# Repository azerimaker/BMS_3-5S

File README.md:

# BMS 3-5S
3-5S Battery Management System based on TI bq76920 IC and MSP430 uC. The design is largely influenced by the TI's [TIDA-00449](http://www.ti.com/tool/TIDA-00449) reference and LibreSolar's excellent [BMS-5s](https://github.com/LibreSolar/BMS-5s) designs.

## Specs:
- 3-5 Li-ion/Po Cells
- MSP430 Microcontroller for gas gauging, balancing and serial communication
- Load current: 50A (cont.), 100A (peak) (estimated!)
- You can find the PCB on Seeedstudio's [Fusion Gallery](https://www.seeedstudio.com/BMS-3-5S-g-1092928)

## Programming
- I'm using MSP430 Launchpad both to program the BMS in external target mode and to provide serial communication to PC. 

## Demo
- After modifying the TIDA-00449 firmware, which was designed for bq76930 (10S version) balancing and status report worked fine [(see here)](https://twitter.com/OrkhanAmirAslan/status/1014643359699406849)

## To Do in next Rev. 
- Add simple Python script to decode serial messages and print cell status
- Fix issues with battery voltage switching and Pre-Discharge mosfets. 
- Remove soldermask for high current tracks. 
- More pads for balancing resistors for higher power dissipation. 

<div align="center">
<br /> This work is licensed under a <a rel="license" href="http://creativecommons.org/licenses/by-sa/4.0/">Creative Commons Attribution-ShareAlike 4.0 International License</a>.

</div>

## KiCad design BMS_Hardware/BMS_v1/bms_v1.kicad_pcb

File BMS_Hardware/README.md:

## BMS 3-5S Hardware Files

KiCAD version 4.0.7 was used.

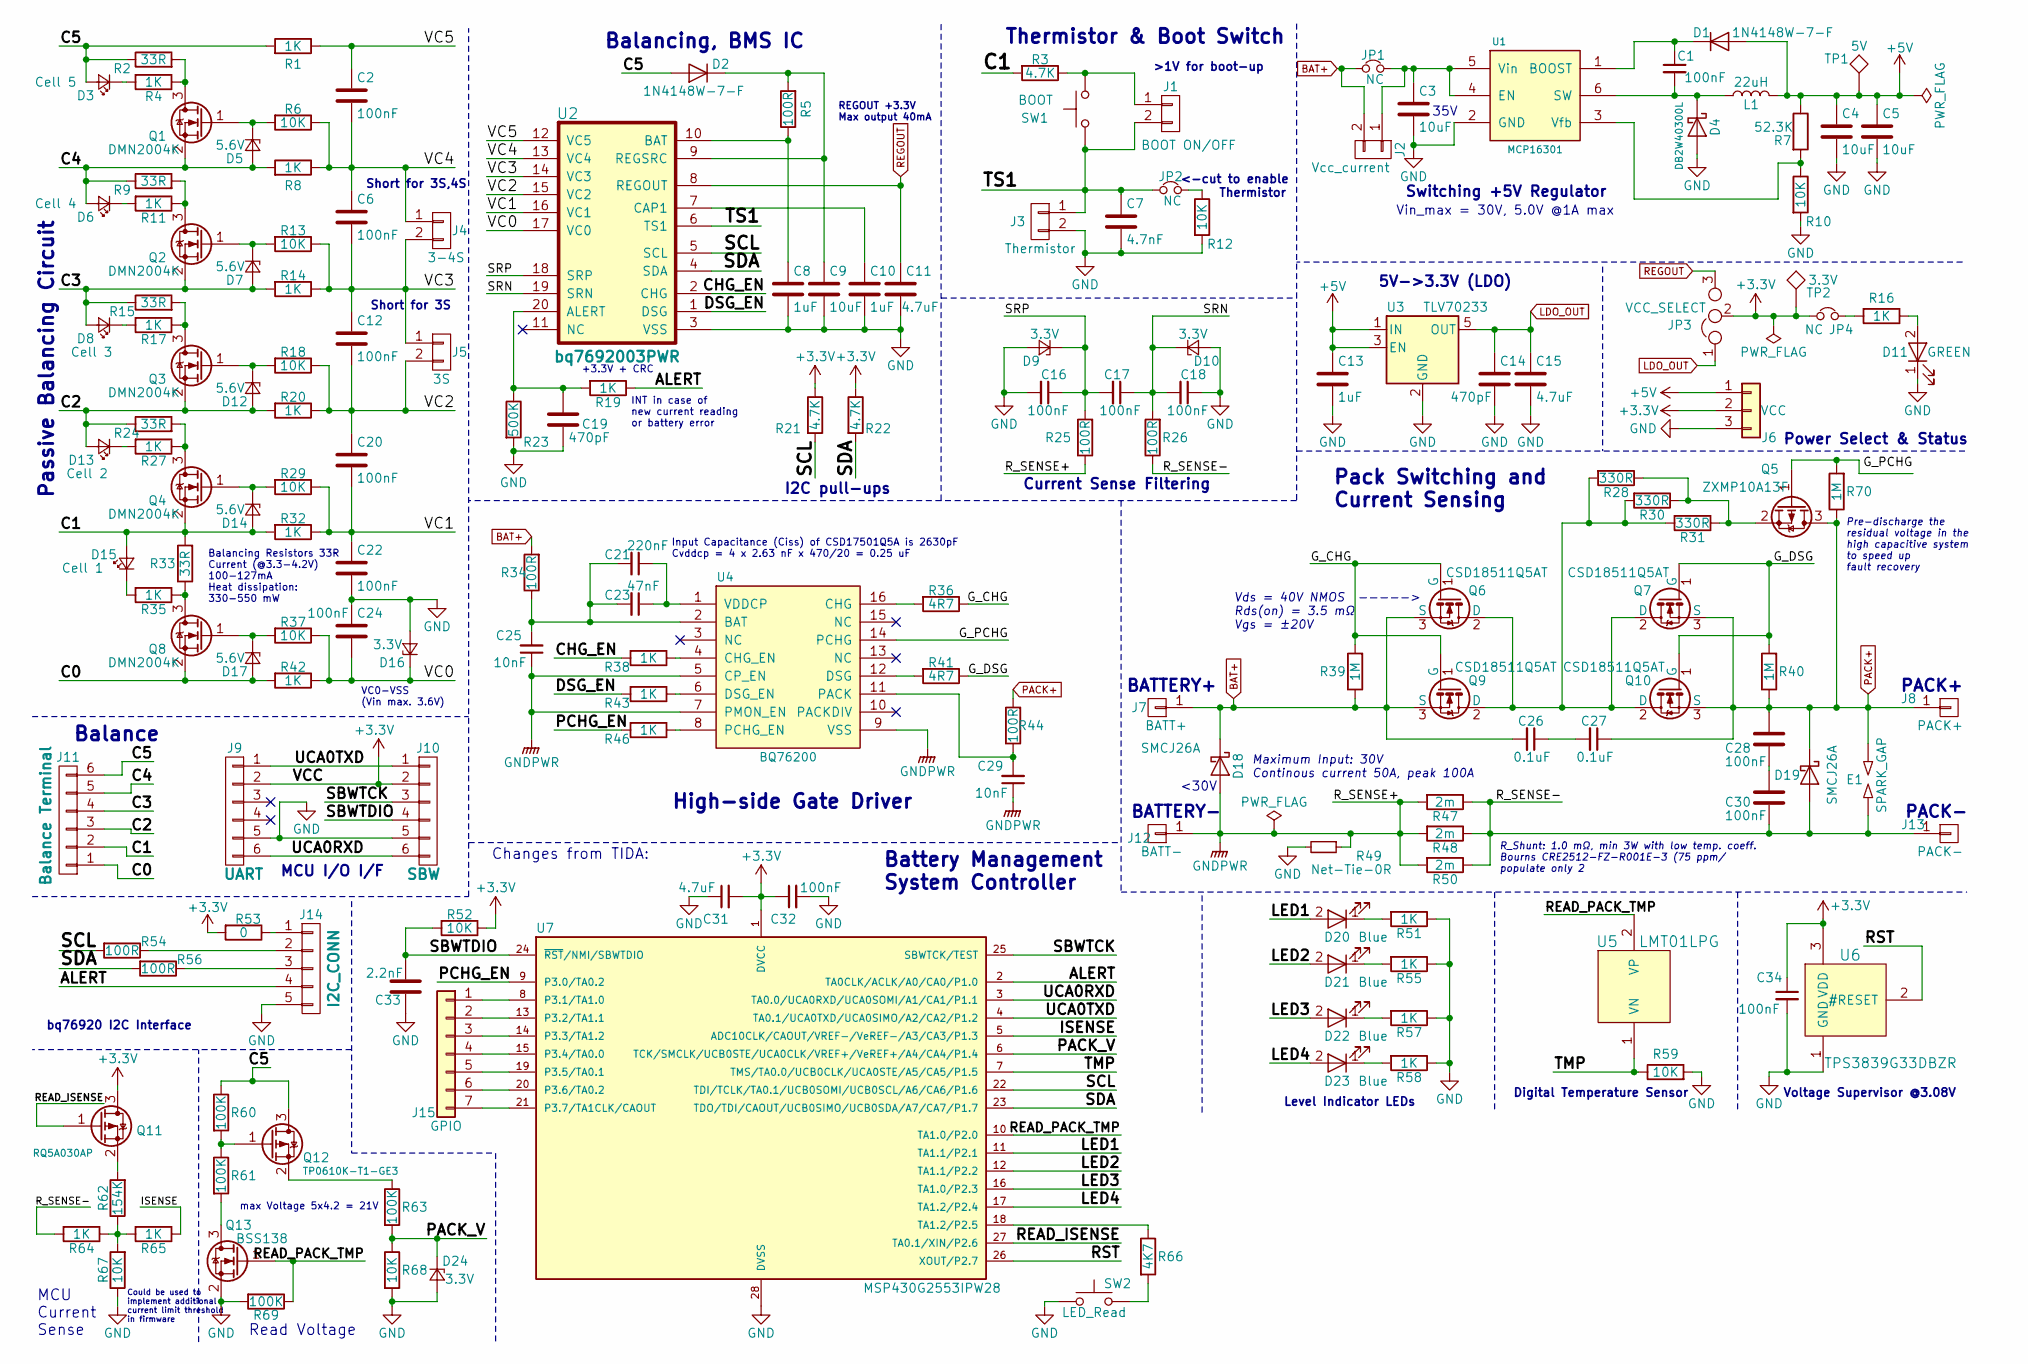
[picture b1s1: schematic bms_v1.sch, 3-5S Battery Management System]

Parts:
C1, C2, C6, C12, C16, C17, C18, C20, C22, C24, C28, C30, C32, C34: 100nF; C_0603
C3, C4, C9: 10uF; C_1210
C5: 10uF; C_0603
C7: 4.7nF; C_0603
C8, C10, C13: 1uF; C_0603
C11, C15, C31: 4.7uF; C_1206
C14, C19: 470pF; C_0603
C21: 220nF; C_0603
C23: 47nF; C_0603
C25, C29: 10nF; C_0603
C26, C27: 0.1uF; C_0603
C33: 2.2nF; C_0603
D1, D2: 1N4148W-7-F; D_SOD-123
D3: Cell 5; LED_0603
D4: DB2W40300L; D_SOD-123F
D5, D7, D12, D14, D17: 5.6V; D_SOD-323
D6: Cell 4; LED_0603
D8: Cell 3; LED_0603
D9, D10, D16, D24: 3.3V; D_SOD-323
D11: GREEN; LED_0603
D13: Cell 2; LED_0603
D15: Cell 1; LED_0603
D18, D19: SMCJ26A; D_SMC
D20, D21, D22, D23: Blue; LED_0603
E1: SPARK_GAP; Spark_Gap_1.65x1.1
J1: BOOT ON/OFF; jumper_NO
J2: Vcc_current; Pin_Header_Straight_1x02_Pitch2.54mm
J3: Thermistor; Test_Point_2Pads
J4: 3-4S; Pin_Header_Straight_1x02_Pitch2.54mm
J5: 3S; Pin_Header_Straight_1x02_Pitch2.54mm
J6: VCC; Pin_Header_Straight_1x03_Pitch2.54mm
J7: BATT+; MountingHole_3.5mm_Pad_Via
J8: PACK+; MountingHole_3.5mm_Pad_Via
J9: UART; Pin_Header_Straight_1x06_Pitch2.54mm
J10: SBW; Pin_Header_Straight_1x06_Pitch1.27mm
J11: Balance Terminal; PhoenixContact_MSTBVA-G_06x5.00mm_Vertical
J12: BATT-; MountingHole_3.5mm_Pad_Via
J13: PACK-; MountingHole_3.5mm_Pad_Via
J14: I2C_CONN; Pin_Header_Straight_1x05_Pitch2.54mm
J15: GPIO; Pin_Header_Straight_1x07_Pitch2.54mm
JP1, JP2, JP4: NC; jumper_NC
JP3: VCC_SELECT; JP_NO_NC
L1: 22uH; L_Taiyo-Yuden_NR-60xx
Q1, Q2, Q3, Q4, Q8: DMN2004K; SOT-23
Q5: ZXMP10A13F; SOT-23
Q6, Q7, Q9, Q10: CSD18511Q5AT; VSONP-8-1EP_5x6_Pitch1.27mm(GDS)
Q11: RQ5A030AP; SuperSOT-3
Q12: TP0610K-T1-GE3; SOT-23
Q13: BSS138; SOT-23
R1, R4, R8, R11, R14, R16, R17, R19, R20, R27, R32, R35, R38, R42, R43, R46, R51, R55, R57, R58, R64, R65: 1K; R_0603
R2, R9, R15, R24, R33: 33R; R_2010_HandSoldering
R3, R21, R22: 4.7K; R_0603
R5, R25, R26, R34, R44, R54, R56: 100R; R_0603
R6, R10, R12, R13, R18, R29, R37, R52, R59, R67, R68: 10K; R_0603
R7: 52.3K; R_0603
R23: 500K; R_0603
R28, R30, R31: 330R; R_0603_HandSoldering
R36, R41: 4R7; R_0603
R39, R40, R70: 1M; R_0603
R47, R48, R50: 2m; R_2512_HandSoldering
R49: Net-Tie-0R; R_0603_HandSoldering
R53: 0; R_0603
R60, R61, R63, R69: 100K; R_0603
R62: 154K; R_0603
R66: 4K7; R_0603
SW1: BOOT; SW_SPST_EVQP2
SW2: LED_Read; SW_SPST_EVQP2
TP1: 5V; Measurement_Point_Round-SMD-Pad_Small
TP2: 3.3V; Measurement_Point_Round-SMD-Pad_Small
U1: MCP16301; SOT-23-6
U2: bq7692003PWR; TSSOP-20_4.4x6.5mm_Pitch0.65mm
U3: TLV70233; SOT-23-5
U4: BQ76200; TSSOP-16_4.4x5mm_Pitch0.65mm
U5: LMT01LPG; Test_Point_2Pads
U6: TPS3839G33DBZR; SOT-23-3
U7: MSP430G2553IPW28; TSSOP-28_4.4x9.7mm_Pitch0.65mm

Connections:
+3V3: C31.2, C32.1, C34.1, J6.2, J9.2, J10.2, JP3.2, JP4.1, Q11.3 (D), R21.1, R22.1, R52.1, R53.2, TP2.1, U6.3 (VDD), U7.1 (DVCC)
+5V: C4.1, C5.1, C13.1, D1.2 (A), J6.1, L1.2, R7.1, TP1.1, U3.1 (IN), U3.3 (EN)
/ALERT: J14.4, R19.1, U7.2 (TA0CLK/ACLK/A0/CA0/P1.0)
/C0: D17.2 (A), J11.1, Q8.2 (S), R42.2
/C1: D14.2 (A), D15.2 (A), J11.2, Q4.2 (S), R3.2, R32.2, R33.2
/C2: D12.2 (A), D13.2 (A), J11.3, Q3.2 (S), R20.2, R24.1
/C3: D7.2 (A), D8.2 (A), J11.4, Q2.2 (S), R14.2, R15.1
/C4: D5.2 (A), D6.2 (A), J11.5, Q1.2 (S), R8.2, R9.1
/C5: D2.2 (A), D3.2 (A), J11.6, Q12.3 (D), R1.2, R2.1, R60.1
/CHG_EN: R38.2, U2.2 (CHG)
/DSG_EN: R43.2, U2.1 (DSG)
/G_CHG: Q6.1 (G), Q9.1 (G), R36.1, R39.2
/G_DSG: Q7.1 (G), Q10.1 (G), R40.2, R41.1
/ISENSE: R65.1, U7.5 (ADC10CLK/CAOUT/VREF-/VeREF-/A3/CA3/P1.3)
/LED1: D20.2 (A), U7.11 (TA1.1/P2.1)
/LED2: D21.2 (A), U7.12 (TA1.1/P2.2)
/LED3: D22.2 (A), U7.16 (TA1.0/P2.3)
/LED4: D23.2 (A), U7.17 (TA1.2/P2.4)
/PACK_V: D24.1 (K), R63.2, R68.1, U7.6 (TCK/SMCLK/UCB0STE/UCA0CLK/VREF+/VeREF+/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)
/PCHG_EN: R46.2, U7.9 (P3.0/TA0.2)
/READ_ISENSE: Q11.1 (G), U7.27 (TA0.1/XIN/P2.6)
/READ_PACK_TMP: Q13.1 (G), R69.1, U5.2 (VP), U7.10 (TA1.0/P2.0)
/RST: U6.2 (#RESET), U7.26 (XOUT/P2.7)
/R_SENSE-: C30.2, D19.2 (A), E1.2, J13.1, R26.1, R47.1, R48.1, R50.1, R64.2
/SBWTCK: J10.3, U7.25 (SBWTCK/TEST)
/SBWTDIO: C33.1, J10.4, R52.2, U7.24 (~RST~/NMI/SBWTDIO)
/SCL: R21.2, R54.2, U2.5 (SCL), U7.22 (TDI/TCLK/TA0.1/UCB0SOMI/UCB0SCL/A6/CA6/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)
/SDA: R22.2, R56.2, U2.4 (SDA), U7.23 (TDO/TDI/CAOUT/UCB0SIMO/UCB0SDA/A7/CA7/P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)
/SRN: C17.1, C18.2, D10.1 (K), R26.2, U2.19 (SRN)
/SRP: C16.1, C17.2, D9.1 (K), R25.2, U2.18 (SRP)
/TMP: R59.1, U5.1 (VN), U7.7 (TMS/TA0.0/UCB0CLK/UCA0STE/A5/CA5/P1.5)
/TS1: C7.1, J1.2, J3.1, JP2.1, SW1.2, U2.6 (TS1)
/UCA0RXD: J9.6, J10.6, U7.3 (TA0.0/UCA0RXD/UCA0SOMI/A1/CA1/P1.1)
/UCA0TXD: J9.1, J10.1, U7.4 (TA0.1/UCA0TXD/UCA0SIMO/A2/CA2/P1.2)
/VC0: C24.2, D16.1 (K), R37.1, R42.1, U2.17 (VC0)
/VC1: C20.2, C22.1, R29.1, R32.1, U2.16 (VC1)
/VC2: C12.2, C20.1, J5.2, R18.1, R20.1, U2.15 (VC2)
/VC3: C6.2, C12.1, J4.2, J5.1, R13.1, R14.1, U2.14 (VC3)
/VC4: C2.2, C6.1, J4.1, R6.1, R8.1, U2.13 (VC4)
/VC5: C2.1, R1.1, U2.12 (VC5)
BAT+: C26.2, D18.1 (K), J2.2, J7.1, JP1.1, Q6.3 (S), Q9.3 (S), R34.2, R39.1
GND: C3.2, C4.2, C5.2, C7.2, C8.2, C9.2, C10.2, C11.2, C13.2, C14.2, C15.2, C16.2, C18.1, C19.2, C22.2, C24.1, C31.1, C32.2, C33.2, C34.2, D4.2 (A), D9.2 (A), D10.2 (A), D11.1 (K), D16.2 (A), D24.2 (A), J3.2, J6.3, J9.5, J10.5, J14.5, Q13.2 (S), R10.2, R12.2, R23.2, R49.2, R51.1, R55.1, R57.1, R58.1, R59.2, R67.1, R68.2, R69.2, SW2.1, U1.2 (GND), U2.3 (VSS), U3.2 (GND), U6.1 (GND), U7.28 (DVSS)
GNDPWR: C25.1, C29.1, D18.2 (A), J12.1, R25.1, R47.2, R48.2, R49.1, R50.2, U4.5 (CP_EN), U4.7 (PMON_EN), U4.9 (VSS)
LDO_OUT: C14.1, C15.1, JP3.1, U3.5 (OUT)
unnamed: C1.1, D1.1 (K), U1.1 (BOOST)
unnamed: C1.2, D4.1 (K), L1.1, U1.6 (SW)
unnamed: C3.1, J2.1, JP1.2, U1.4 (EN), U1.5 (Vin)
unnamed: C8.1, R5.1, U2.10 (BAT)
unnamed: C9.1, D2.1 (K), R5.2, U2.9 (REGSRC)
unnamed: C10.1, U2.7 (CAP1)
unnamed: C19.1, R19.2, R23.1, U2.20 (ALERT)
unnamed: C21.1, C23.1, U4.1 (VDDCP)
unnamed: C21.2, C23.2, C25.2, R34.1, U4.2 (BAT)
unnamed: C26.1, C27.2
unnamed: C28.2, C30.1
unnamed: C29.2, R44.1, U4.11 (PACK)
unnamed: D3.1 (K), R4.2
unnamed: D5.1 (K), Q1.1 (G), R6.2
unnamed: D6.1 (K), R11.2
unnamed: D7.1 (K), Q2.1 (G), R13.2
unnamed: D8.1 (K), R17.2
unnamed: D11.2 (A), R16.1
unnamed: D12.1 (K), Q3.1 (G), R18.2
unnamed: D13.1 (K), R27.2
unnamed: D14.1 (K), Q4.1 (G), R29.2
unnamed: D15.1 (K), R35.2
unnamed: D17.1 (K), Q8.1 (G), R37.2
unnamed: D20.1 (K), R51.2
unnamed: D21.1 (K), R55.2
unnamed: D22.1 (K), R57.2
unnamed: D23.1 (K), R58.2
unnamed: J1.1, R3.1, SW1.1
unnamed: J14.1, R53.1
unnamed: J14.2, R54.1
unnamed: J14.3, R56.1
unnamed: J15.1, U7.8 (P3.1/TA1.0)
unnamed: J15.2, U7.13 (P3.2/TA1.1)
unnamed: J15.3, U7.14 (P3.3/TA1.2)
unnamed: J15.4, U7.15 (P3.4/TA0.0)
unnamed: J15.5, U7.19 (P3.5/TA0.1)
unnamed: J15.6, U7.20 (P3.6/TA0.2)
unnamed: J15.7, U7.21 (P3.7/TA1CLK/CAOUT)
unnamed: JP2.2, R12.1
unnamed: JP4.2, R16.2
unnamed: Q1.3 (D), R2.2, R4.1
unnamed: Q2.3 (D), R9.2, R11.1
unnamed: Q3.3 (D), R15.2, R17.1
unnamed: Q4.3 (D), R24.2, R27.1
unnamed: Q5.1 (G), R70.2
unnamed: Q5.2 (S), R28.1, R30.1, R31.1
unnamed: Q8.3 (D), R33.1, R35.1
unnamed: Q6.2 (D), Q7.2 (D), Q9.2 (D), Q10.2 (D), R28.2, R30.2, R31.2
unnamed: Q11.2 (S), R62.2
unnamed: Q12.1 (G), R60.2, R61.1
unnamed: Q12.2 (S), R63.1
unnamed: Q13.3 (D), R61.2
unnamed: R7.2, R10.1, U1.3 (Vfb)
unnamed: R36.2, U4.16 (CHG)
unnamed: R38.1, U4.4 (CHG_EN)
unnamed: R41.2, U4.12 (DSG)
unnamed: R43.1, U4.6 (DSG_EN)
unnamed: R46.1, U4.8 (PCHG_EN)
unnamed: R62.1, R64.1, R65.2, R67.2
unnamed: R66.1, U7.18 (TA1.2/P2.5)
unnamed: R66.2, SW2.2
PACK+: C27.1, C28.1, D19.1 (K), E1.1, J8.1, Q5.3 (D), Q7.3 (S), Q10.3 (S), R40.1, R44.2, R70.1
REGOUT: C11.1, JP3.3, U2.8 (REGOUT)

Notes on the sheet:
Balancing, BMS IC
Battery Management System Controller
MCU I/O I/F
<-cut to enable Thermistor
BATTERY-
BATTERY+
PACK-
PACK+
REGOUT +3.3V Max output 40mA
Thermistor & Boot Switch
bq76920 I2C Interface
Power Select & Status
R_Shunt: 1.0 mΩ, min 3W with low temp. coeff. Bourns CRE2512-FZ-R001E-3 (75 ppm/ populate only 2
MCU Current Sense
Read Voltage
Digital Temperature Sensor
Voltage Supervisor @3.08V
Short for 3S
Short for 3S,4S
Balancing Resistors 33R Current (@3.3-4.2V) 100-127mA Heat dissipation: 330-550 mW
Passive Balancing Circuit
VC0-VSS (Vin max. 3.6V)
INT in case of new current reading or battery error
+3.3V + CRC
>1V for boot-up
I2C pull-ups
35V
Switching +5V Regulator
Vin_max = 30V, 5.0V @1A max
5V->3.3V (LDO)
<30V
Current Sense Filtering
Maximum Input: 30V Continous current 50A, peak 100A
Changes from TIDA:
Pre-discharge the residual voltage in the high capacitive system to speed up fault recovery
Pack Switching and Current Sensing
Balance
Input Capacitance (Ciss) of CSD17501Q5A is 2630pF Cvddcp = 4 x 2.63 nF x 470/20 = 0.25 uF
High-side Gate Driver
Vds = 40V NMOS -----> Rds(on) = 3.5 mΩ Vgs = ±20V

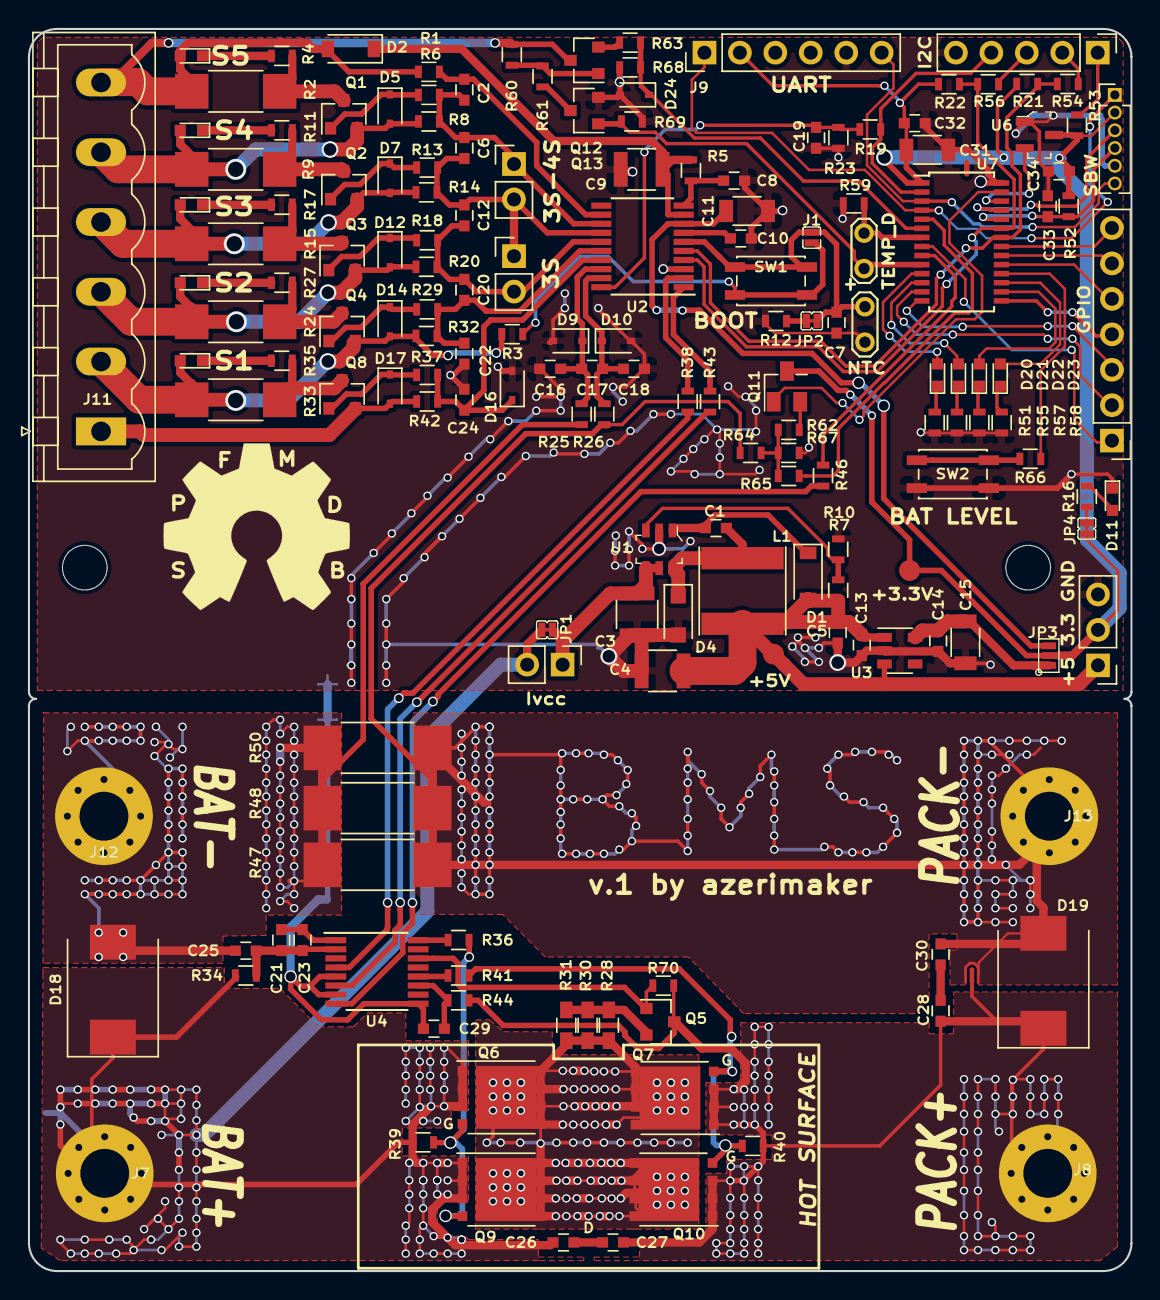
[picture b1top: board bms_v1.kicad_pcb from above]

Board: 2 copper layers, 79.0 x 89.0 mm, 172 parts (1 on the bottom side), 107 nets.

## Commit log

2018-02-09 BMS_v1 HW files
    BMS_v1 is my first attempt to produce 3-5S BMS board. Board is largely modified around the reference design TIDA-00449 from TI.
2018-02-09 Adding BMSv1 render
2018-02-09 Fixing path
2018-02-09 Fixing links
2018-02-09 BMS 3D render added
2018-02-09 Readme
2018-02-09 Sch added
2018-02-15 addings PCB pic
2018-02-15 adding issues
2018-03-17 initial version of the firmware
    This is the initial version of the bms_v1 firmware, it's not not finished. Use at your own risk.
2018-07-05 demo added
2018-07-05 To do added
2018-07-05 pcb link added
2018-07-05 readme fix
2018-07-05 kicad note
